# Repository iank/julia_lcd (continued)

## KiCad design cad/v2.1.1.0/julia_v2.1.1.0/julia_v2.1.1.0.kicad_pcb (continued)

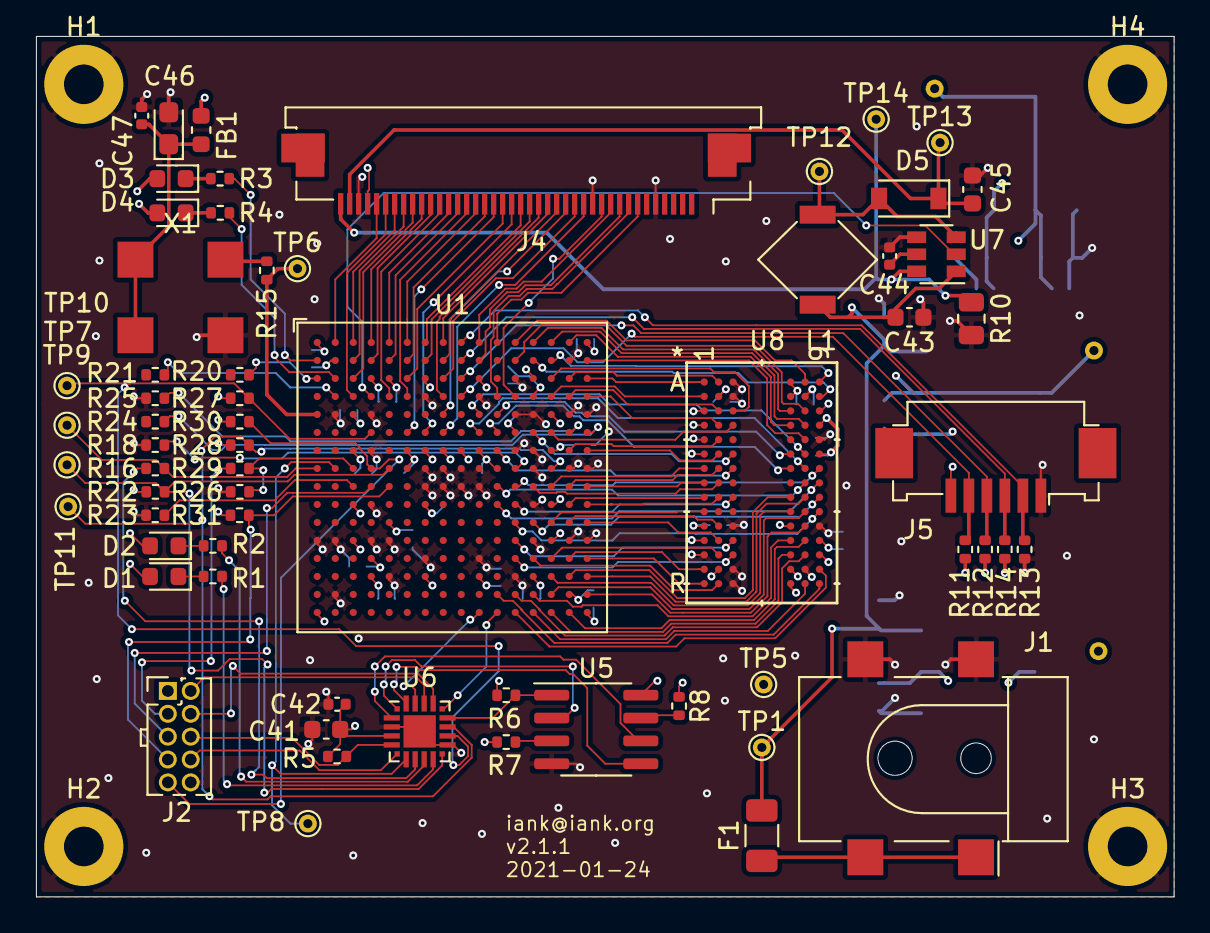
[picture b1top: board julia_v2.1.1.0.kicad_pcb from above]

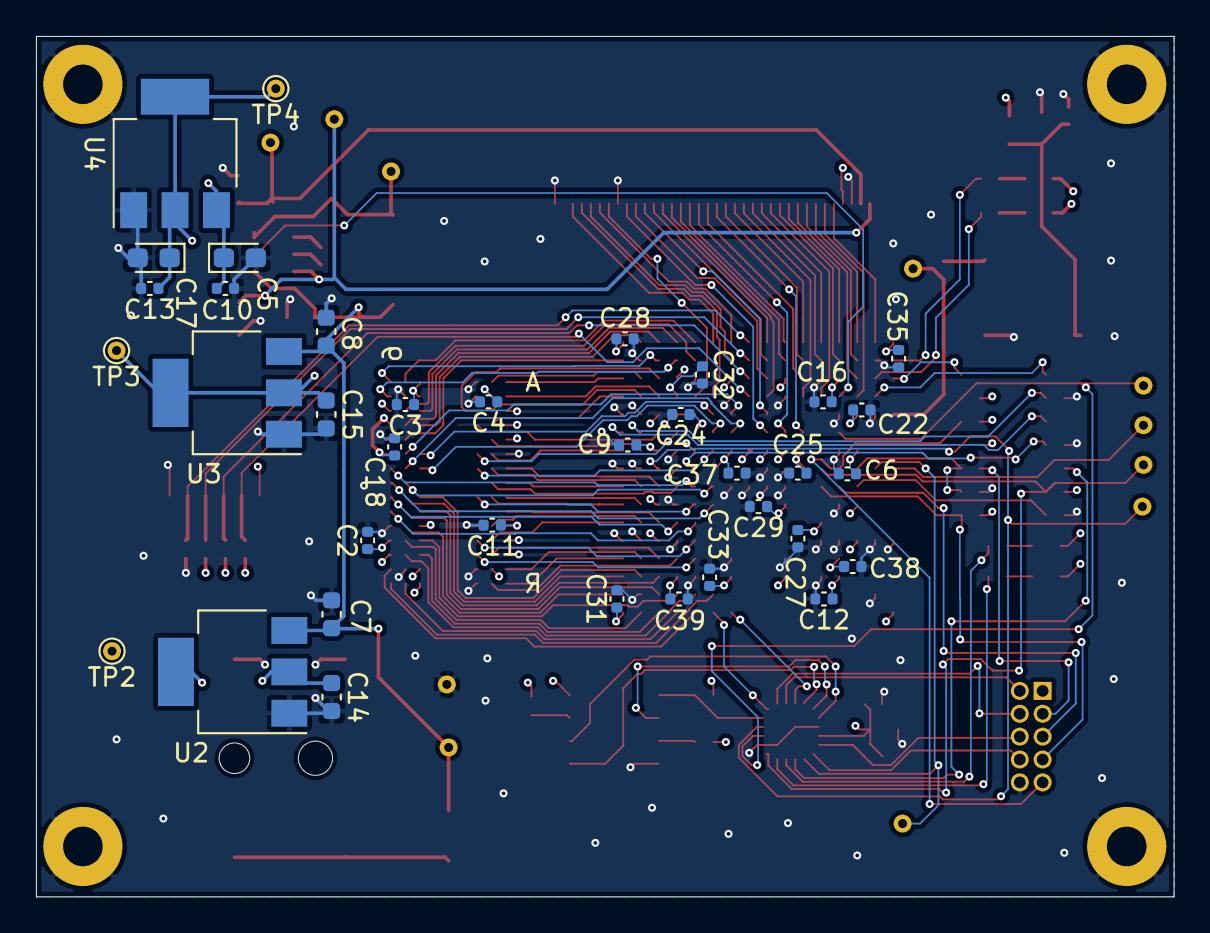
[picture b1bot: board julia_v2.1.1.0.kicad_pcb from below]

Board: 4 copper layers, 63.2 x 47.8 mm, 104 parts (36 on the bottom side), 140 nets.

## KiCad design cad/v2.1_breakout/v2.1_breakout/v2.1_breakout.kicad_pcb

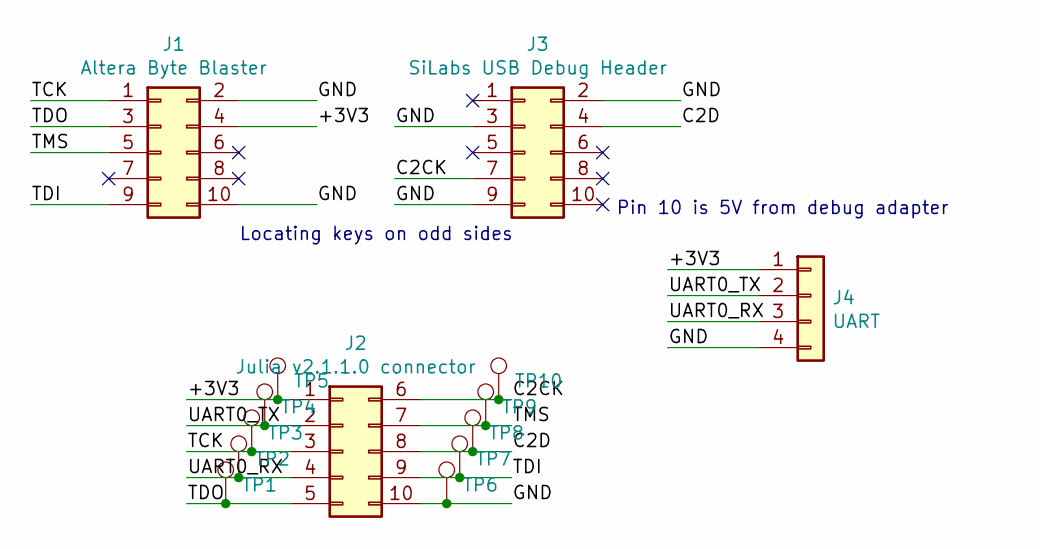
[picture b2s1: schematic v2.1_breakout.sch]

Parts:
J1: Altera Byte Blaster; PinHeader_2x05_P2.54mm_Vertical
J2: Julia v2.1.1.0 connector; PinHeader_2x05_P1.27mm_Vertical
J3: SiLabs USB Debug Header; PinHeader_2x05_P2.54mm_Vertical
J4: UART; PinHeader_1x04_P2.54mm_Vertical
TP1, TP2, TP3, TP4, TP5, TP6, TP7, TP8, TP9, TP10: TestPoint; TestPoint_THTPad_D1.0mm_Drill0.5mm

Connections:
/+3V3: J1.4, J2.1, J4.1, TP5.1
/C2CK: J2.6, J3.7, TP10.1
/C2D: J2.8, J3.4, TP8.1
/GND: J1.2, J1.10, J2.10, J3.2, J3.3, J3.9, J4.4, TP6.1
/TCK: J1.1, J2.3, TP3.1
/TDI: J1.9, J2.9, TP7.1
/TDO: J1.3, J2.5, TP1.1
/TMS: J1.5, J2.7, TP9.1
/UART0_RX: J2.4, J4.3, TP2.1
/UART0_TX: J2.2, J4.2, TP4.1

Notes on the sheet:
Locating keys on odd sides
Pin 10 is 5V from debug adapter

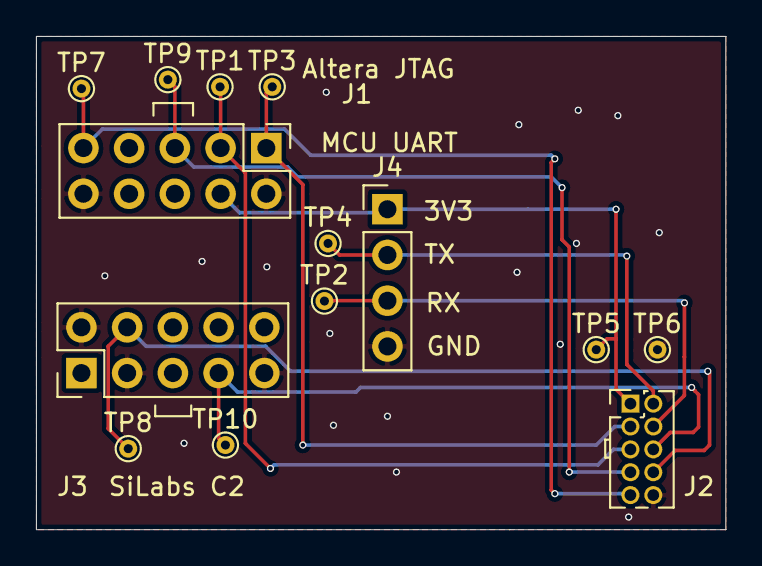
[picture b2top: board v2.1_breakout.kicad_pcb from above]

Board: 2 copper layers, 38.3 x 27.4 mm, 14 parts (0 on the bottom side), 10 nets.

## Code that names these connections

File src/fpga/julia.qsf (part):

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set_location_assignment PIN_B3 -to RGB[3]
set_location_assignment PIN_A3 -to RGB[2]
set_location_assignment PIN_D3 -to RGB[1]
set_location_assignment PIN_D12 -to LCDCLK
set_location_assignment PIN_A11 -to DEN
set_location_assignment PIN_D11 -to VSD
set_location_assignment PIN_B10 -to HSD
set_location_assignment PIN_A10 -to STBYB
set_global_assignment -name ENABLE_OCT_DONE OFF
set_global_assignment -name ENABLE_CONFIGURATION_PINS OFF
set_global_assignment -name ENABLE_BOOT_SEL_PIN OFF
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set_global_assignment -name POWER_PRESET_COOLING_SOLUTION "23 MM HEAT SINK WITH 200 LFPM AIRFLOW"
set_global_assignment -name POWER_BOARD_THERMAL_MODEL "NONE (CONSERVATIVE)"
set_global_assignment -name GENERATE_RBF_FILE ON
set_location_assignment PIN_D4 -to LIGHT
set_location_assignment PIN_C9 -to SCL
set_location_assignment PIN_B9 -to SDA
set_location_assignment PIN_A9 -to TOUCH_INTN
set_location_assignment PIN_D9 -to TOUCH_RSTN
set_global_assignment -name VERILOG_FILE backlight.v
set_global_assignment -name VERILOG_FILE ft5426.v
set_global_assignment -name VERILOG_FILE axis_fifo.v
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
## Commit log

2020-11-01 LCD/memory Breakout
2020-11-01 Images
2020-11-01 Board image URL
2020-11-01 Higher resolution board image
2020-11-29 Datasheets
2020-11-29 (Buggy) verilog PoC, drives screen and SRAM
2020-11-29 Fix image link in README
2020-11-29 Move v1.0.0.0 files into version directory
2020-11-29 ECNs for v1.0.0.0
2020-11-29 Fix J5 and D1 footprints in version v1.1.0.0 (not verified)
2020-12-03 v2 WiP
2020-12-04 v2 update, power and config chip
2020-12-04 Julia v2.0.0.0 schematic and BOM
2020-12-06 Julia v2.0.0.0 board
2020-12-06 v2.0.0.0 images
2020-12-06 CAM files for v2.0.0.0
2020-12-06 Update v2 status
2020-12-26 Update verilog for v2.0.0.0 board
2020-12-26 More aggressive SRAM timing; clean up top-level FSM
2021-01-01 Extremely low-precision mandelbrot (probably)
2021-01-04 v2.1.0.0 schematic
2021-01-06 Swap FAN5333BSX backlight driver for TPS61165
2021-01-08 v2.1.0.0: changed connector, ERC, annotation/footprint assignment
2021-01-09 Layout begun
2021-01-09 Layout complete(?)
2021-01-09 v2.1.0.0 gerber files
2021-01-10 Programmer breakout board for v2.1
2021-01-25 v2.1.1
2021-01-28 v2.1.1.0 BOM
2021-02-12 Clean up v2.1.1.0 FPGA sheet; update BOM
2021-02-12 Gitignore
2021-02-12 Clean up old versions, add pdf/png outputs
2021-02-12 Empty design w/ pin assignments
2021-02-13 Verilog: Video out
2021-02-13 Test fixtures for LCD and SDRAM controllers
2021-02-13 SDRAM to display FIFO (simulates but doesn't work)
2021-02-13 Fix refresh timing (still doesn't work in HW)
2021-02-14 System definition
2021-02-14 Generated BSP and project
2021-02-14 S_DQ inout -_-
2021-02-16 stable test pattern (sim/actual)
2021-02-16 rm nios
2021-02-16 Pixel fifo mixed width; Add simulation tools; verilog sim matches actual, a both a little off from JS
2021-02-17 pixel FIFO high/low thresholds
2021-02-17 Move video side of FIFO to separate file
2021-02-17 Fix tabs
2021-02-17 Rearrange some signals
2021-02-17 Sweep SDRAM init / frame reading under the rug
2021-02-17 Add SDRAM controller mux
2021-02-17 Split mem init out of frame reader
2021-02-17 Add SOF
2021-02-18 (probably working) arbitration btwn frame reader and processor
2021-02-19 processor reads/edits/writes back
2021-02-20 Update IP
2021-02-20 akxlcrakpc.ladgl.
2021-02-20 Giving up on that last thing
2021-02-20 processor checks fifo status
2021-02-20 Two processor FIFOs
2021-02-20 Test: slow down processing
2021-02-20 Fix pixel addition
2021-02-21 Clean up processor state machine
2021-02-21 processor read/write xy data
2021-02-21 Verify processor read/write xy data
2021-02-21 Update barrel jack footprint
2021-02-21 Several more 3d models
2021-02-21 Updated 3d rendering
2021-02-21 Updated 3d rendering (bottom)
2021-02-21 dual-clock FIFOs, match width.. haven't verified data
2021-02-21 Verified
2021-02-21 combine a couple signals
2021-02-21 Move math processor into module
2021-02-23 Mandelbrot. (video still misaligned)
2021-02-26 Fix FIFO overrun leading to misalignment
2021-02-26 Reasonable color map for now
2021-02-26 Increase processor clock to 20MHz
2021-02-26 Store iteration separately from pixel color
2021-02-26 MCU: blinky
2021-02-26 MCU: UART0 demo
2021-02-27 SPI flash init
2021-02-27 Move SPI flash routines out of main
2021-02-27 Refactor SPI flash init
2021-02-27 Command/response; erase chip
2021-02-27 Write and dump memory
2021-02-27 Increase SPI clock to 1.5MHz
2021-02-28 configure FPGA
2021-03-09 Generate a (particular) julia set
2021-03-09 Generate color map
2021-03-09 Draw julia or mandelbrot
2021-03-09 Overlay julia on mandelbrot
2021-03-26 Julia set constant from pixel value
2021-03-27 Touch control
2021-03-27 Clear+redraw julia when touch registers
2021-03-27 Zoom/center
2021-04-06 Color map hack for immediate feedback on touch; blank screen/backlight after couple minutes
